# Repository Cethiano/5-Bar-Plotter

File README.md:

2DOF Plotter using a 5 bar linkage.

I made this because I thought 5 bar linkages seemed really cool. Also I wanted to learn inverse kinematics (it was hard) and stepper motor control.

3D Model

PCB

BOM 
| Part                     | Quantity | Link                                                                   |
|--------------------------|----------|------------------------------------------------------------------------|
| Nema 17 Stepper Motor    | 2        | https://www.amazon.com/gp/product/B0B93L4H57?smid=AWQBCGWISS7BL&psc=1  |
| A4988 Stepper Controller | 2        | https://www.amazon.com/gp/product/B0DQGPP7DL?smid=A24KRRWWW1U0PG&psc=1 |
| 12v power supply         | 1        | https://www.amazon.com/gp/product/B091XSVV1Y?smid=A3RVBXPX8VM3VL&psc=1 |
| ESP32                    | 1        | https://www.amazon.com/gp/product/B08D5ZD528?smid=A2Z10KY0342329&psc=1 |
| Motor Holding Plate      | 1        | 3D Models Folder                                                       |
| Motor Arm                | 2        | 3D Models Folder                                                       |
| Extension Arm            | 1        | 3D Models Folder                                                       |
| Marker Holding Arm       | 1        | 3D Models Folder                                                       |
| PCB                      | 1        | PCB Folder                                                             |
| Female Pin Headers x19   | 2        | https://www.adafruit.com/product/598                                   |
| Female Pin Headers x8    | 4        | https://www.adafruit.com/product/598                                   |
| Male Pin Headers x4      | 2        | https://www.adafruit.com/product/392                                   |
| Male Pin Headers x1      | 1        | https://www.adafruit.com/product/392                                   |
| Capacitor 100uf          | 1        | https://www.digikey.com/en/products/detail/panasonic-electronic-components/EEU-FC2A101/285728                               |

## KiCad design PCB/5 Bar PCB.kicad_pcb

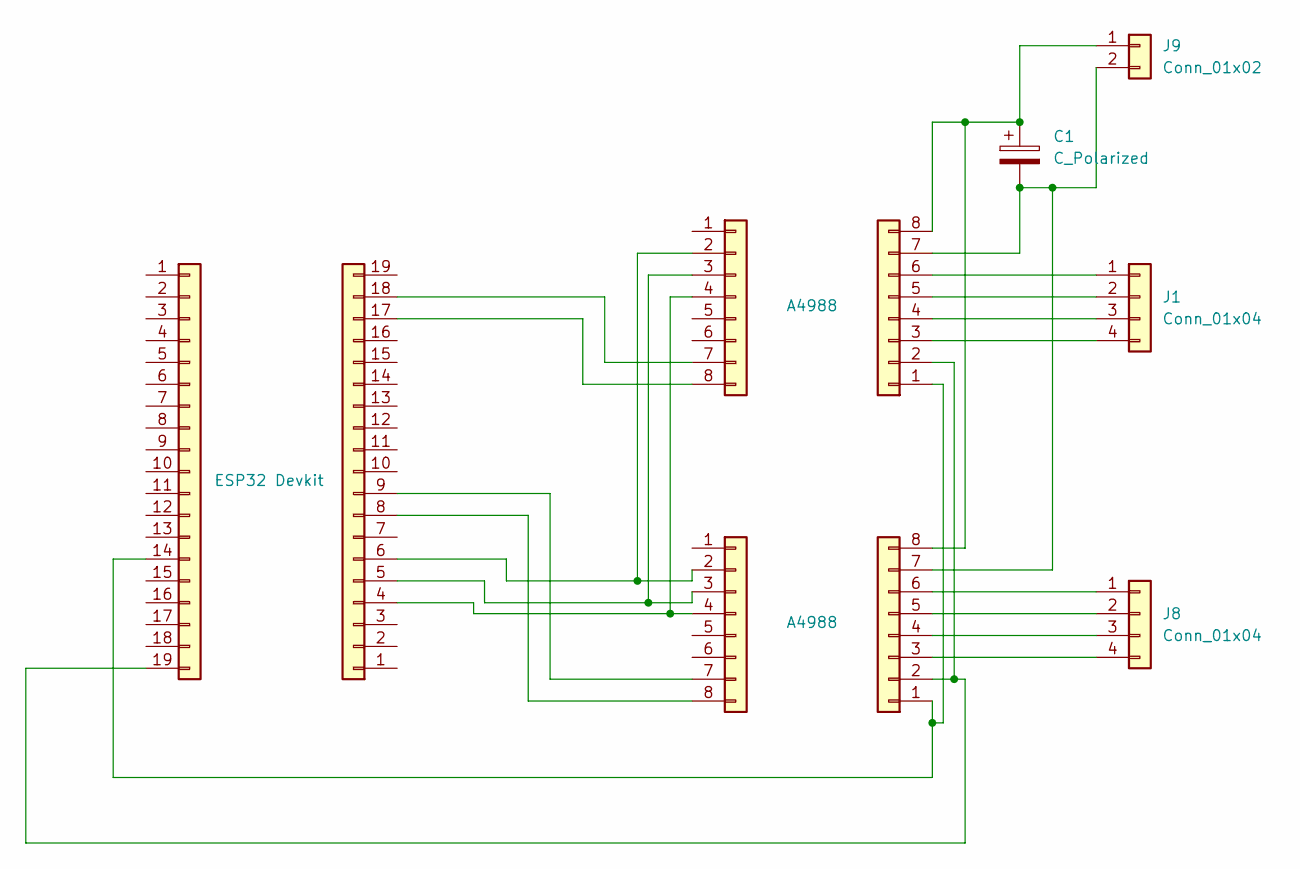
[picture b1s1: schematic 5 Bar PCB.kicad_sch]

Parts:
C1: C_Polarized; CP_Radial_D6.3mm_P2.50mm
J1, J8: Conn_01x04; PinHeader_1x04_P2.54mm_Vertical
J2, J7: A4988; PinSocket_1x08_P2.54mm_Vertical
J3, J6: Conn_01x08; PinSocket_1x08_P2.54mm_Vertical
J4: ESP32 Devkit; PinSocket_1x19_P2.54mm_Vertical
J5: Conn_01x19; PinSocket_1x19_P2.54mm_Vertical
J9: Conn_01x02; PinHeader_1x02_P2.54mm_Vertical

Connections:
unnamed: J1.1, J2.6
unnamed: J1.2, J2.5
unnamed: J1.3, J2.4
unnamed: J1.4, J2.3
unnamed: J2.1, J4.14, J7.1
unnamed: J2.2, J4.19, J7.2
unnamed: C1.2, J2.7, J7.7, J9.2
unnamed: C1.1, J2.8, J7.8, J9.1
unnamed: J3.2, J5.6, J6.2
unnamed: J3.3, J5.5, J6.3
unnamed: J3.4, J5.4, J6.4
unnamed: J3.7, J5.18
unnamed: J3.8, J5.17
unnamed: J5.8, J6.8
unnamed: J5.9, J6.7
unnamed: J7.3, J8.4
unnamed: J7.4, J8.3
unnamed: J7.5, J8.2
unnamed: J7.6, J8.1

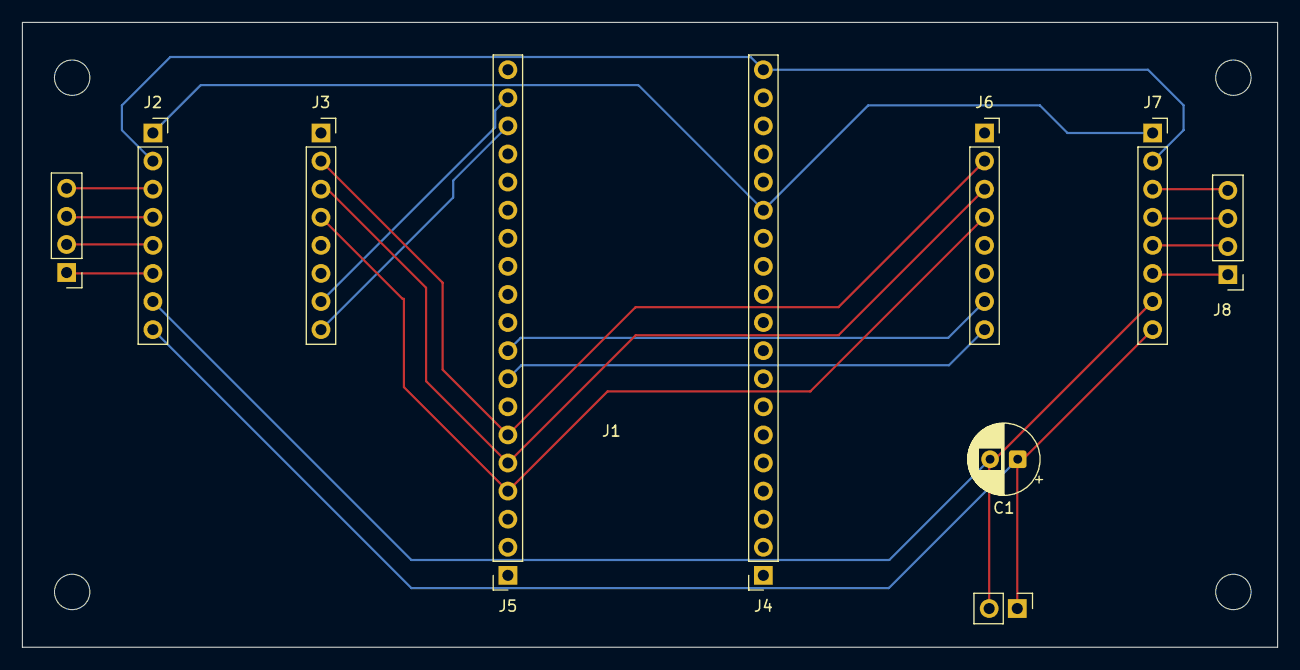
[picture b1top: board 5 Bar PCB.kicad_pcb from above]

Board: 2 copper layers, 113.5 x 56.5 mm, 10 parts (0 on the bottom side), 19 nets.

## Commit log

2026-03-23 added everything
2026-03-23 organized stuff
2026-03-23 added 3d models
